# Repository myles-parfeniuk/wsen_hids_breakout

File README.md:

<summary>Table of Contents</summary>
<ol>
<li><a href="#about">About</a></li>
<li><a href="#pcbway-sponsorship">PCBWay Sponsorship</a></li>
<li><a href="#gerber-files">Gerber Files</a></li>
<li><a href="#pcb-renders">PCB Renders</a></li>
<li><a href="#schematic-and-layout">Schematic and Layout</a></li>
<li><a href="#operating-voltages">Operating Voltages</a></li>
<li><a href="#contact">Contact</a></li>
</ol>

# About
Breakout board for [Würth Elektronik 2525020210002](https://www.we-online.com/en/components/products/WSEN-HIDS) I2C humidity w/ integrated temperature sensor IC.   
This repo contains all the schematic and layout files in the form of a KiCad project, they can be found within the `kicad` directory.
<p align="right">(<a href="#readme-top">back to top</a>)</p>

# PCBWay Sponsorship
Special thanks to PCBWay for reaching out to sponsor this project and provide access to their excellent service.  
PCBWay supports the DIY and open source community as well as students with sponsorships and contests frequently.   
Show them some love and consider having your next project fabricated by them: 

Order [here](https://www.pcbway.com/) today.

The boards manufactured by PCBWay had quality that exceeded my expectations.  
The silk screen was less smudged and noticeably more detailed than other fab houses I've used before. All 5 of the boards in my order had no defects, both cosmetic, and functionally.   

The shipping was also insanely quick; I live overseas from China, despite that, with standard shipping the boards were at my place within 2 weeks of uploading the gerbers.    
Their website also had an easy to follow [guide](https://www.pcbway.com/blog/help_center/Generate_Gerber_file_from_Kicad.html) on the settings they require for generated gerbers, this made ordering a breeze. Their [capabilities page](https://www.pcbway.com/capabilities.html) was also easy to follow for setting the constraints within KiCad.  

Overall, I was very satisfied with the result, I'll definitely be using them for any future projects.  

**NOTE:**  

The renders look different from the photos below, as these were for revision 1.0. The renders and KiCad files are for the newest revision, 1.1.

<p align="right">(<a href="#readme-top">back to top</a>)</p>

# Gerber Files
Generated gerber and drill files can be found within the gerbers.7z archive.   
These files were generated according to PCBWay's desired settings, thus, they can be used to order the boards from them without re-plotting.
<p align="right">(<a href="#readme-top">back to top</a>)</p>

# PCB Renders

<p align="right">(<a href="#readme-top">back to top</a>)</p>

# Schematic and Layout

<p align="right">(<a href="#readme-top">back to top</a>)</p>

# Operating Voltages
| Pin | Min.| Max. |
|----------|----------|----------|
| 3v3    | 1.08  | 3.6   |
| SCL/SDA    | -0.3  | 3.9  |
<p align="right">(<a href="#readme-top">back to top</a>)</p>

# Contact
Myles Parfeniuk — myles.parfenyuk@gmail.com  

Project Link — [myles-parfeniuk/wsen_hids_breakout](myles-parfeniuk/wsen_hids_breakout)
<p align="right">(<a href="#readme-top">back to top</a>)</p>

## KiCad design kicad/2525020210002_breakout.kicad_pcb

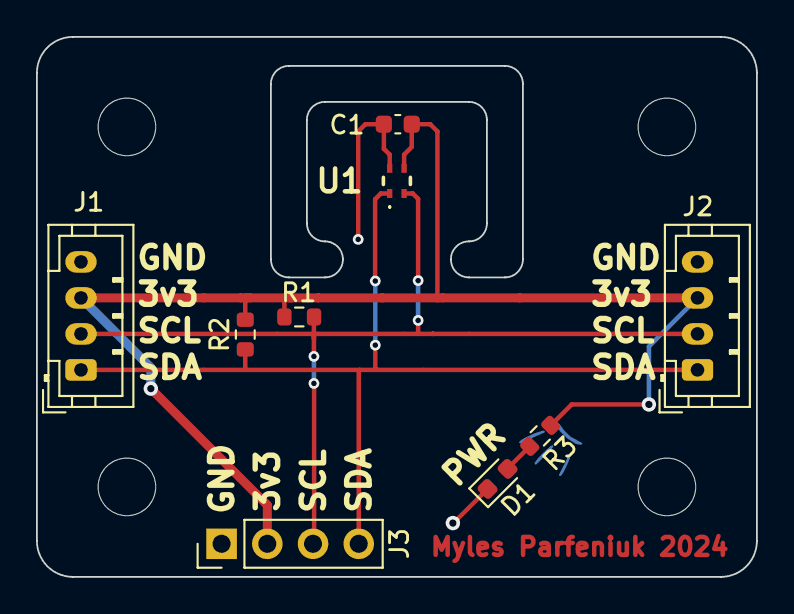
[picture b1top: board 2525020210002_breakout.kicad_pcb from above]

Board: 2 copper layers, 40.0 x 30.0 mm, 13 parts (0 on the bottom side), 5 nets.

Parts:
C1: 100n; C_0603_1608Metric
D1: 150060VS7500; LED_0603_1608Metric
H1, H2, H3, H4: MountingHole M3; MountingHole_3.2mm_M3
J1, J2: JST_PH_B4B-PH-K; JST_PH_B4B-PH-K_1x04_P2.00mm_Vertical
J3: Conn_01x04_Socket; PinHeader_1x04_P2.54mm_Vertical
R1, R2: 10k; R_0603_1608Metric
R3: 4.7K; R_0603_1608Metric
U1: 2525020210002

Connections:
+3V3: C1.1, J1.3, J2.3, J3.2, R1.2, R2.2, R3.2, U1.3 (VDD)
/I2C1_SCL: J1.2, J2.2, J3.3, R1.1, U1.2 (SCL)
/I2C1_SDA: J1.1, J2.1, J3.4, R2.1, U1.1 (SDA)
GND: C1.2, D1.1 (K), J1.4, J2.4, J3.1, U1.4 (VSS)
unnamed: D1.2 (A), R3.1

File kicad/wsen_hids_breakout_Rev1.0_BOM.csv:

#,Reference,Qty,Value,Footprint,Digikey Product #
1,C1,1,100n,Capacitor_SMD:C_0603_1608Metric,311-1341-2-ND
2,D1,1,LED,LED_SMD:LED_0603_1608Metric,732-4980-2-ND
3,"J1, J2",2,JST_PH_B4B-PH-K,Connector_JST:JST_PH_B4B-PH-K_1x04_P2.00mm_Vertical,455-B4B-PH-K-ND
4,"J1, J2",2,JST_PH_B4B-PH-K,Connector_JST:JST_PH_B4B-PH-K_1x04_P2.00mm_Vertical,455-1164-ND
5,J3,1,Conn_01x04_Socket,Connector_PinHeader_2.54mm:PinHeader_1x04_P2.54mm_Vertical,n/a
6,"R1, R2",2,10k,Resistor_SMD:R_0603_1608Metric,RMCF0603JT10K0TR-ND
7,R3,1,4.7K,Resistor_SMD:R_0603_1608Metric,RMCF0603FT4K70TR-ND
8,U1,1,2525020210002,BiltongBoardSensorExpansion:2525020210002,732-2525020210002TR-ND

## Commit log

2024-10-10 added kicad project files
2024-10-10 fixed old image (no 3d model)
2024-10-10 README.md update, schematic m.hole sz lbl
2024-10-10 cleared old backups
2024-10-10 fixed pin name in README.md
2024-10-10 README.md typo fix
2024-10-10 fxd exposed gnd, add r.ss lbls, PCBWay sponsorship
2024-10-11 fixed all DRC violations
2024-10-11 modified pwr diode trace
2024-10-11 generated gerber+drill files
2024-10-11 added layout photo to README.md
2024-10-16 changed solid ground connections to thermal reliefs
2024-10-22 generated BOM, fixed fab layer error
2024-10-23 missing LED part no.
2024-12-06 Swapped SDA & SCL pins, rounded edgecuts
